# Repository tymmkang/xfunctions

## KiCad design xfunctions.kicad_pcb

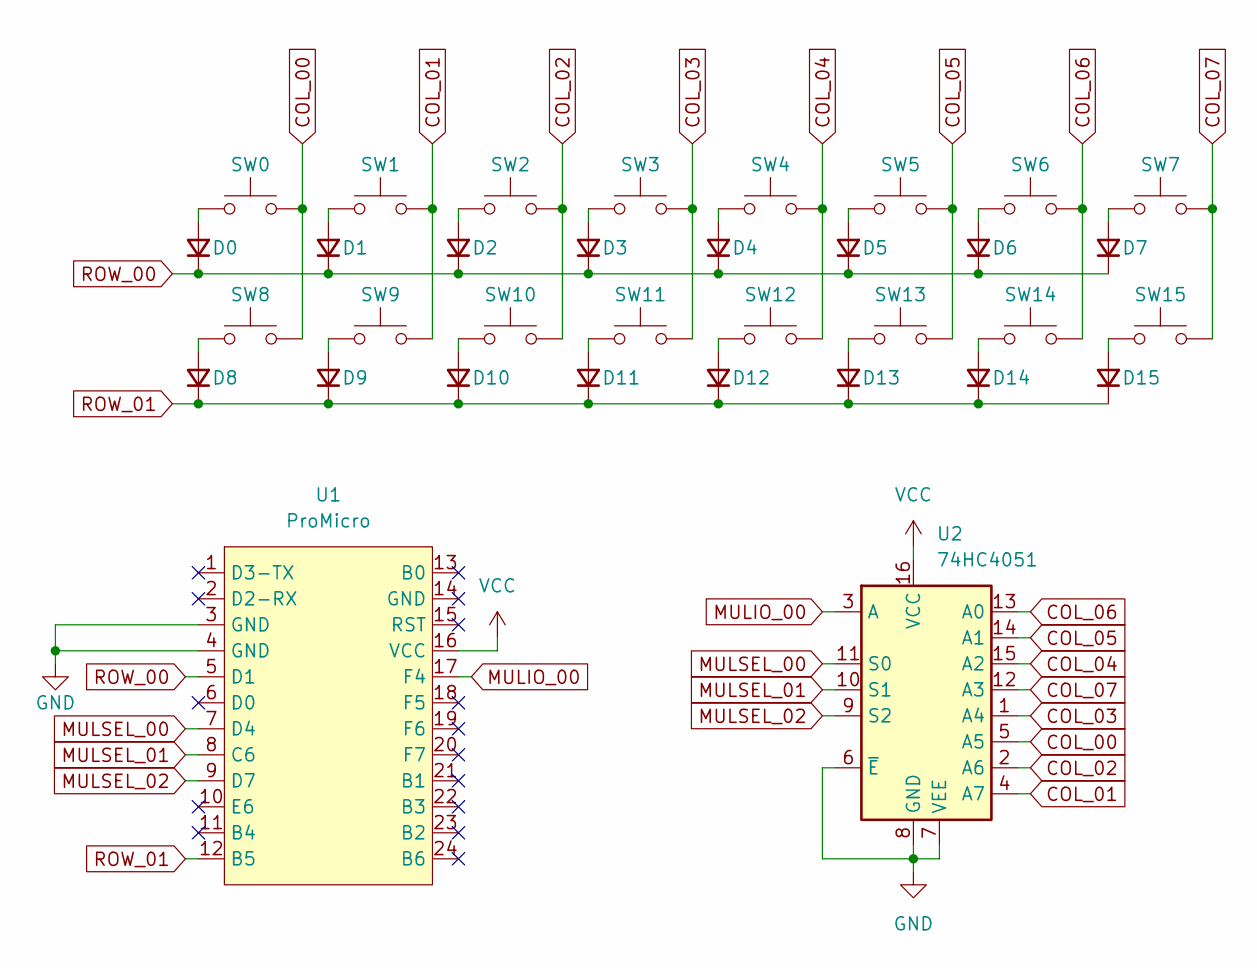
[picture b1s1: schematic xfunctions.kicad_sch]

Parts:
D0, D1, D2, D3, D4, D5, D6, D7, D8, D9, D10, D11, D12, D13, D14, D15: D_Small; D_SOD-323; LCSC C6423741
SW0, SW1, SW2, SW3, SW4, SW5, SW6, SW7, SW8, SW9, SW10, SW11, SW12, SW13, SW14, SW15: SW_Push; SW_MX_HS_CPG151101S11_1u
U1: ProMicro; ProMicro_USBup
U2: 74HC4051; SO-16_3.9x9.9mm_P1.27mm

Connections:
COL_00: SW0.2, SW8.2, U2.5 (A5)
COL_01: SW1.2, SW9.2, U2.4 (A7)
COL_02: SW2.2, SW10.2, U2.2 (A6)
COL_03: SW3.2, SW11.2, U2.1 (A4)
COL_04: SW4.2, SW12.2, U2.15 (A2)
COL_05: SW5.2, SW13.2, U2.14 (A1)
COL_06: SW6.2, SW14.2, U2.13 (A0)
COL_07: SW7.2, SW15.2, U2.12 (A3)
GND: U1.3 (GND), U1.4 (GND), U2.6 (~E), U2.7 (VEE), U2.8 (GND)
MULIO_00: U1.17 (F4), U2.3 (A)
MULSEL_00: U1.7 (D4), U2.11 (S0)
MULSEL_01: U1.8 (C6), U2.10 (S1)
MULSEL_02: U1.9 (D7), U2.9 (S2)
unnamed: D0.2 (A), SW0.1
unnamed: D1.2 (A), SW1.1
unnamed: D2.2 (A), SW2.1
unnamed: D3.2 (A), SW3.1
unnamed: D4.2 (A), SW4.1
unnamed: D5.2 (A), SW5.1
unnamed: D6.2 (A), SW6.1
unnamed: D7.2 (A), SW7.1
unnamed: D8.2 (A), SW8.1
unnamed: D9.2 (A), SW9.1
unnamed: D10.2 (A), SW10.1
unnamed: D11.2 (A), SW11.1
unnamed: D12.2 (A), SW12.1
unnamed: D13.2 (A), SW13.1
unnamed: D14.2 (A), SW14.1
unnamed: D15.2 (A), SW15.1
ROW_00: D0.1 (K), D1.1 (K), D2.1 (K), D3.1 (K), D4.1 (K), D5.1 (K), D6.1 (K), D7.1 (K), U1.5 (D1)
ROW_01: D8.1 (K), D9.1 (K), D10.1 (K), D11.1 (K), D12.1 (K), D13.1 (K), D14.1 (K), D15.1 (K), U1.12 (B5)
VCC: U1.16 (VCC), U2.16 (VCC)

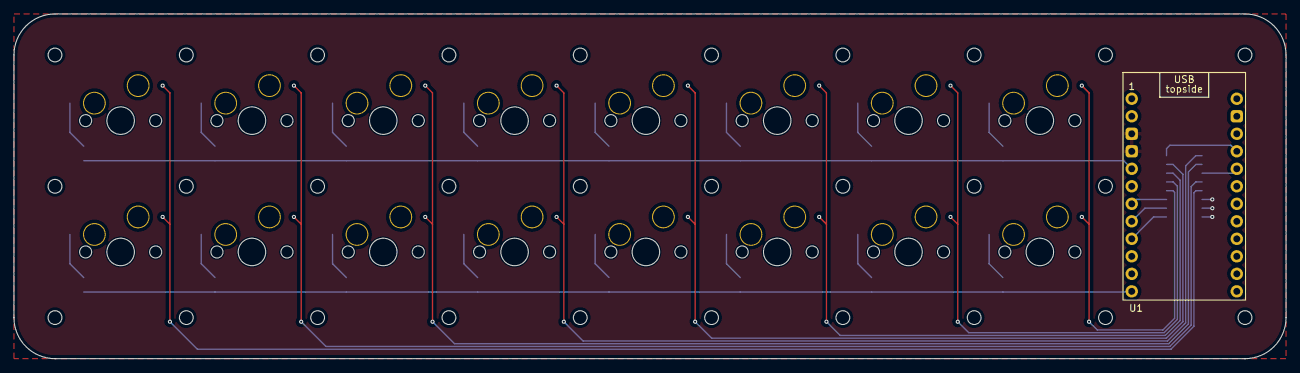
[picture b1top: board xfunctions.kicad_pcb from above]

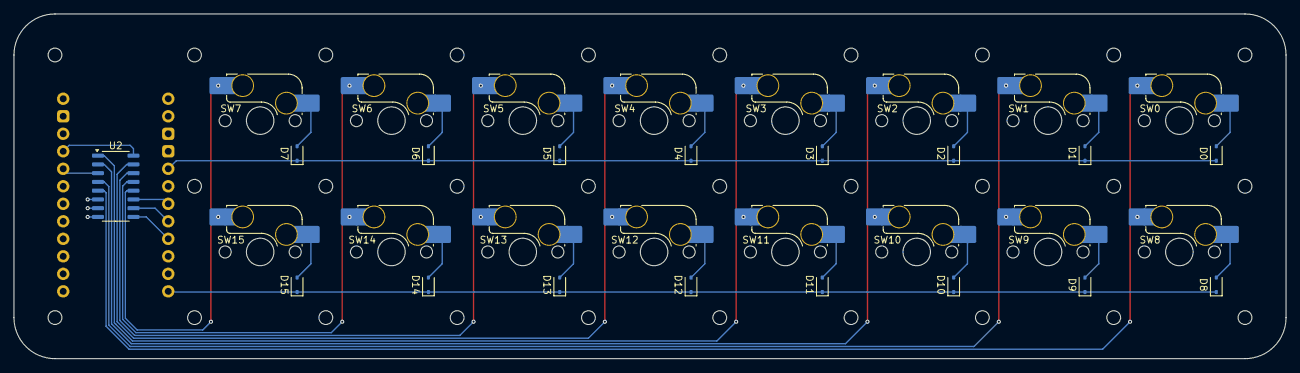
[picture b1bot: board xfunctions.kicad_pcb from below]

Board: 2 copper layers, 184.5 x 50.0 mm, 34 parts (33 on the bottom side), 32 nets.

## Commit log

2024-11-09 저장소 초기화
2024-11-09 프로젝트 추가
2024-11-09 공백 시트 추가
2024-11-09 시트 변경
2024-11-09 SparkFun 보드 심볼, 풋프린트 파일 추가
2024-11-09 SparkFun 보드 심볼, 풋프린트 등록
2024-11-09 스키메틱 작성
2024-11-09 스키메틱 수정
2024-11-09 PCB 작성 완료
2024-11-09 리드미 수정
